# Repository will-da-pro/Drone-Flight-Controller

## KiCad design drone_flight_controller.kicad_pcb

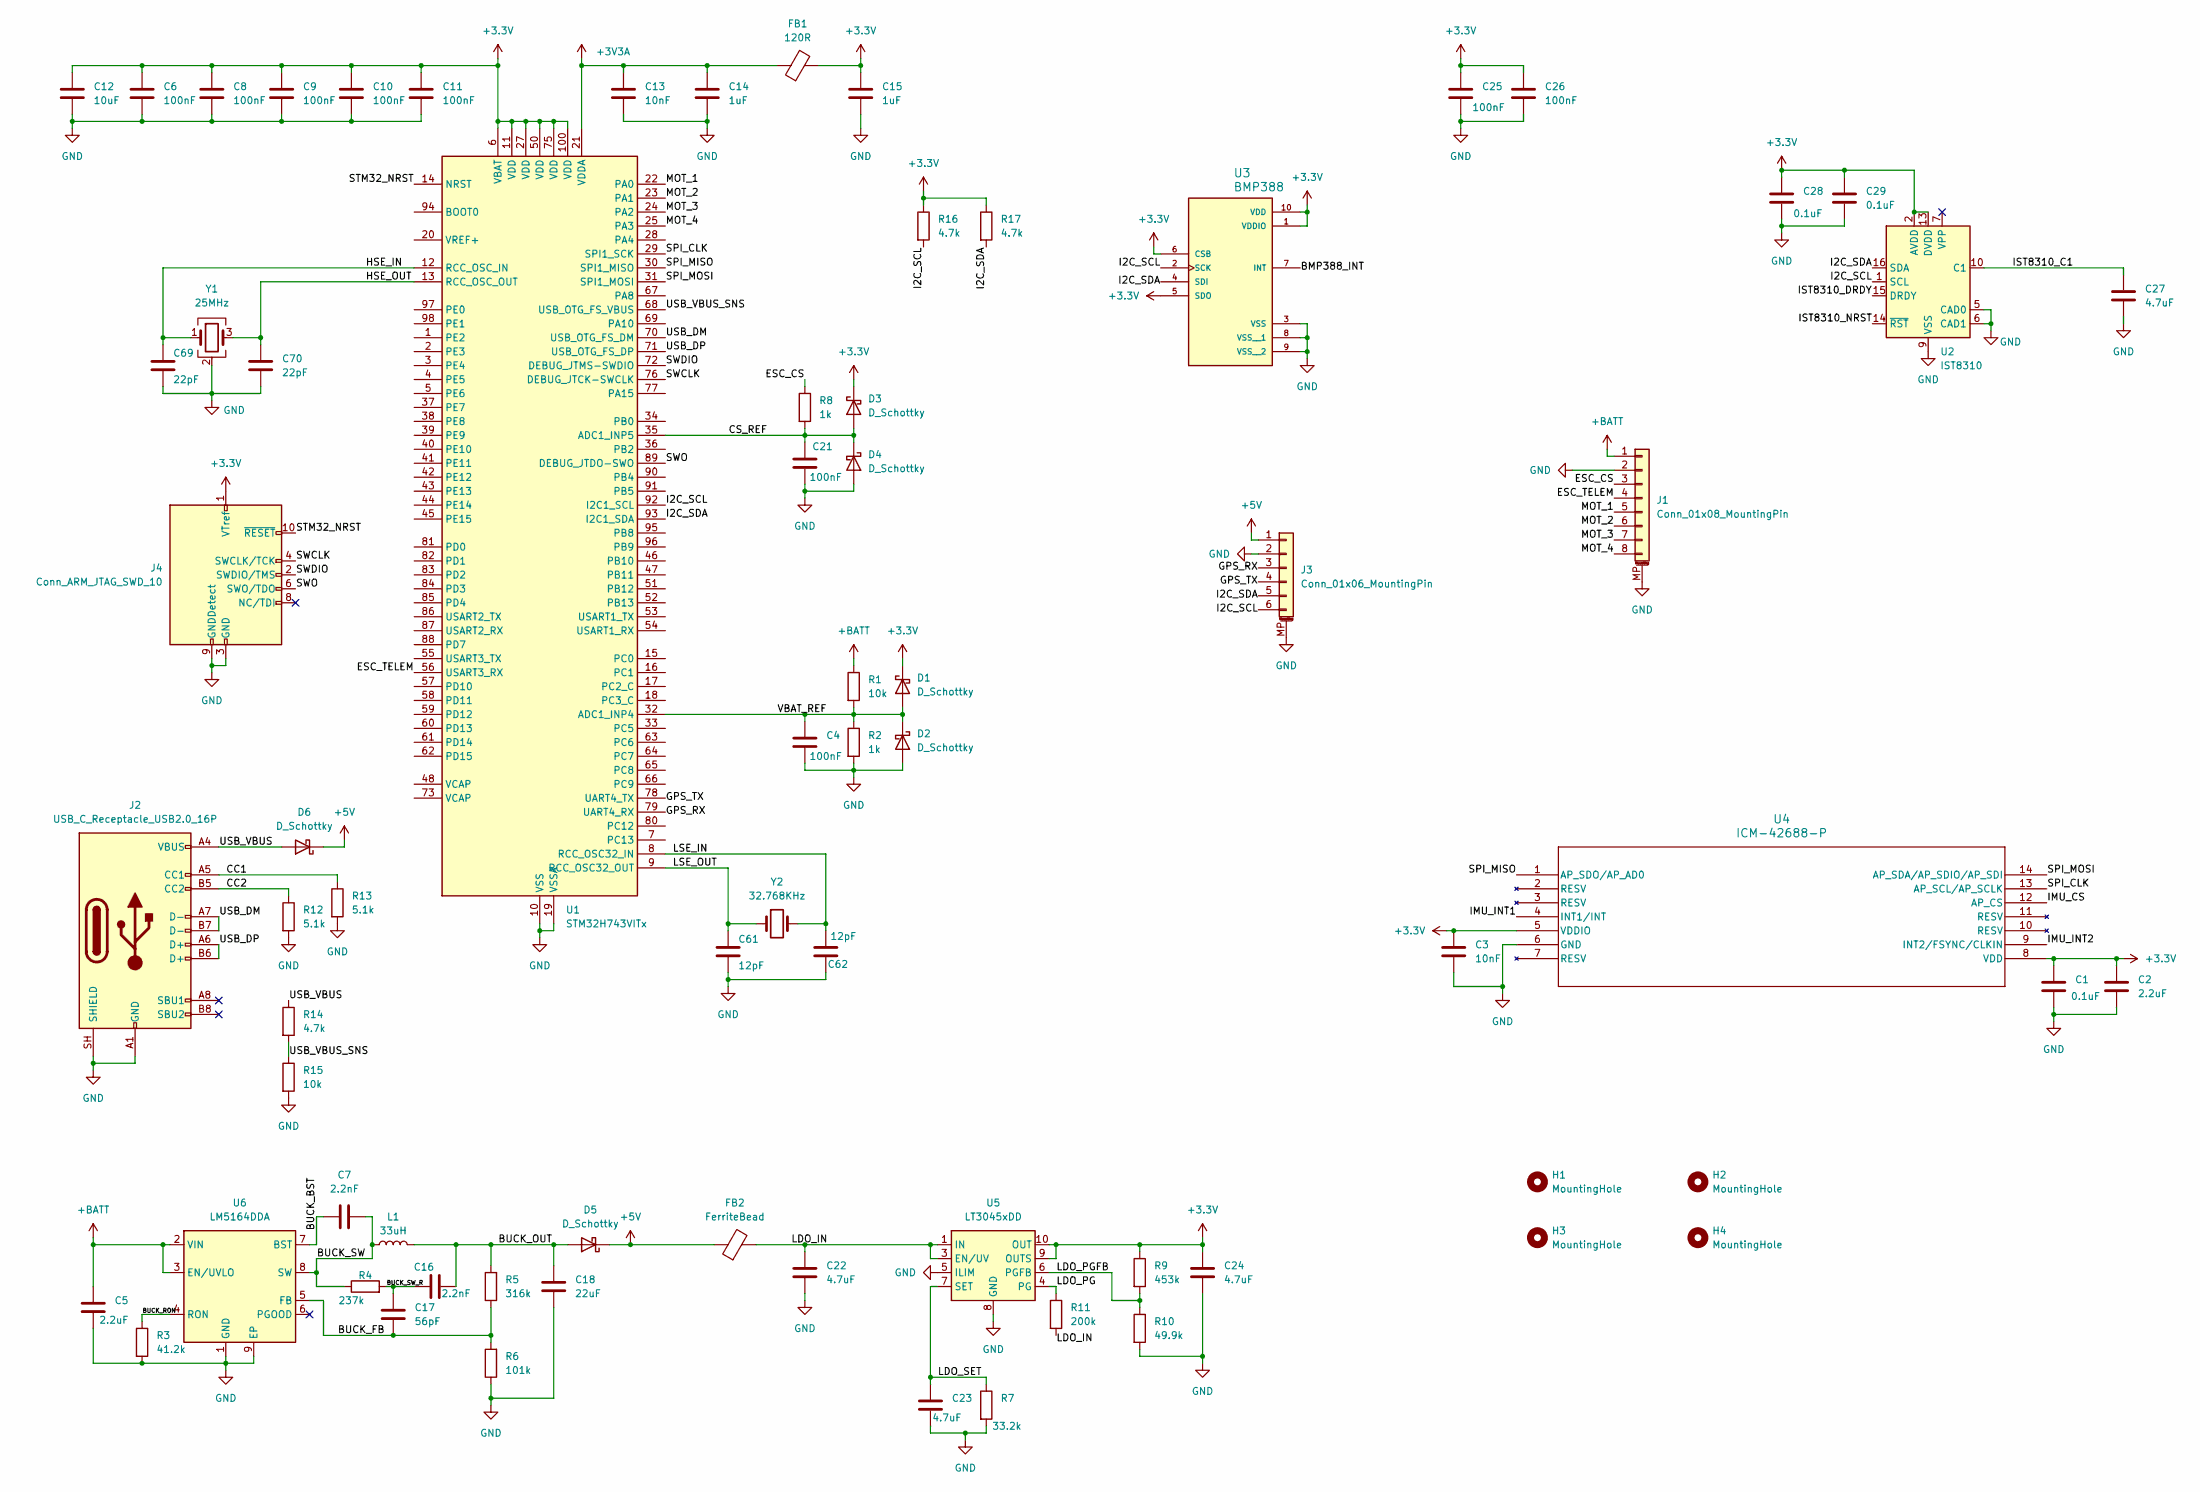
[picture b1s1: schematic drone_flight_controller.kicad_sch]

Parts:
C1, C28, C29: 0.1uF; C_0402_1005Metric
C2, C5: 2.2uF; C_0402_1005Metric
C3: 10nF; C_0402_1005Metric
C4, C21, C25, C26: 100nF; C_0402_1005Metric
C6, C8, C9, C10, C11: 100nF; C_0402_1005Metric; LCSC C307331
C7, C16: 2.2nF; C_0402_1005Metric
C12: 10uF; C_0603_1608Metric; LCSC C96446
C13: 10nF; C_0402_1005Metric; LCSC C15195
C14, C15: 1uF; C_0402_1005Metric; LCSC C52923
C17: 56pF; C_0402_1005Metric
C18: 22uF; C_0603_1608Metric
C22, C24: 4.7uF; C_0603_1608Metric
C23, C27: 4.7uF; C_0402_1005Metric
C61, C62: 12pF; C_0402_1005Metric; LCSC C76948
C69, C70: 22pF; C_0402_1005Metric; LCSC C76960
D1, D2, D3, D4: D_Schottky; D_0402_1005Metric
D5, D6: D_Schottky; D_SOD-123
FB1: 120R; L_0603_1608Metric; LCSC C113030
FB2: FerriteBead; L_0603_1608Metric
H1, H2, H3, H4: MountingHole; MountingHole_2.2mm_M2
J1: Conn_01x08_MountingPin; JST_SH_SM08B-SRSS-TB_1x08-1MP_P1.00mm_Horizontal
J2: USB_C_Receptacle_USB2.0_16P; USB_C_Receptacle_GCT_USB4085
J3: Conn_01x06_MountingPin; JST_SH_SM06B-SRSS-TB_1x06-1MP_P1.00mm_Horizontal
J4: Conn_ARM_JTAG_SWD_10; PinHeader_2x05_P1.27mm_Vertical
L1: 33uH; L_Vishay_IHLP-2525
R1, R15: 10k; R_0402_1005Metric
R2, R8: 1k; R_0402_1005Metric
R3: 41.2k; R_0402_1005Metric
R4: 237k; R_0402_1005Metric
R5: 316k; R_0402_1005Metric
R6: 101k; R_0402_1005Metric
R7: 33.2k; R_0402_1005Metric
R9: 453k; R_0402_1005Metric
R10: 49.9k; R_0402_1005Metric
R11: 200k; R_0402_1005Metric
R12, R13: 5.1k; R_0402_1005Metric
R14, R16, R17: 4.7k; R_0402_1005Metric
U1: STM32H743VITx; LQFP-100_14x14mm_P0.5mm
U2: IST8310; LGA-16_3x3mm_P0.5mm
U3: BMP388; XDCR_BMP388; PARTREV 1.7
U4: ICM-42688-P; LGA-14_3x2.5mm_P0.5mm_LayoutBorder3x4y
U5: LT3045xDD; DFN-10-1EP_3x3mm_P0.5mm_EP1.65x2.38mm
U6: LM5164DDA; HSOP-8-1EP_3.9x4.9mm_P1.27mm_EP2.41x3.1mm_ThermalVias
Y1: 25MHz; Crystal_SMD_3225-4Pin_3.2x2.5mm; LCSC C5444544
Y2: 32.768KHz; Crystal_SMD_3215-2Pin_3.2x1.5mm; LCSC C99010

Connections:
+3.3V: C1.1, C2.1, C3.1, C6.1, C8.1, C9.1, C10.1, C11.1, C12.1, C15.1, C24.1, C25.1, C26.1, C28.1, C29.1, D1.1 (K), D3.1 (K), FB1.2, J4.1 (VTref), R9.1, R16.1, R17.1, U1.6 (VBAT), U1.11 (VDD), U1.27 (VDD), U1.50 (VDD), U1.75 (VDD), U1.100 (VDD), U2.2 (AVDD), U2.13 (DVDD), U3.1 (VDDIO), U3.5 (SDO), U3.6 (CSB), U3.10 (VDD), U4.5 (VDDIO), U4.8 (VDD), U5.9 (OUTS), U5.10 (OUT)
+3V3A: C13.1, C14.1, FB1.1, U1.21 (VDDA)
+5V: D5.1 (K), D6.1 (K), FB2.1, J3.1
+BATT: C5.1, J1.1, R1.1, U6.2 (VIN), U6.3 (EN/UVLO)
/BMP388_INT: U3.7 (INT)
/BUCK_BST: C7.1, U6.7 (BST)
/BUCK_FB: C17.1, R5.1, R6.2, U6.5 (FB)
/BUCK_OUT: C16.2, C18.2, D5.2 (A), L1.2, R5.2
/BUCK_RON: R3.1, U6.4 (RON)
/BUCK_SW: C7.2, L1.1, R4.1, U6.8 (SW)
/BUCK_SW_R: C16.1, C17.2, R4.2
/CC1: J2.A5 (CC1), R13.1
/CC2: J2.B5 (CC2), R12.1
/CS_REF: C21.1, D3.2 (A), D4.1 (K), R8.2, U1.35 (ADC1_INP5)
/ESC_CS: J1.3, R8.1
/ESC_TELEM: J1.4, U1.56 (USART3_RX)
/GPS_RX: J3.3, U1.79 (UART4_RX)
/GPS_TX: J3.4, U1.78 (UART4_TX)
/HSE_IN: C69.1, U1.12 (RCC_OSC_IN), Y1.1
/HSE_OUT: C70.1, U1.13 (RCC_OSC_OUT), Y1.3
/I2C_SCL: J3.6, R16.2, U1.92 (I2C1_SCL), U2.1 (SCL), U3.2 (SCK)
/I2C_SDA: J3.5, R17.2, U1.93 (I2C1_SDA), U2.16 (SDA), U3.4 (SDI)
/IMU_CS: U4.12 (AP_CS)
/IMU_INT1: U4.4 (INT1/INT)
/IMU_INT2: U4.9 (INT2/FSYNC/CLKIN)
/IST8310_C1: C27.1, U2.10 (C1)
/IST8310_DRDY: U2.15 (DRDY)
/IST8310_NRST: U2.14 (~RST)
/LDO_IN: C22.1, FB2.2, R11.2, U5.1 (IN), U5.2 (IN), U5.3 (EN/UV)
/LDO_PG: R11.1, U5.4 (PG)
/LDO_PGFB: R9.2, R10.1, U5.6 (PGFB)
/LDO_SET: C23.1, R7.1, U5.7 (SET)
/LSE_IN: C62.1, U1.8 (RCC_OSC32_IN), Y2.2
/LSE_OUT: C61.1, U1.9 (RCC_OSC32_OUT), Y2.1
/MOT_1: J1.5, U1.22 (PA0)
/MOT_2: J1.6, U1.23 (PA1)
/MOT_3: J1.7, U1.24 (PA2)
/MOT_4: J1.8, U1.25 (PA3)
/SPI_CLK: U1.29 (SPI1_SCK), U4.13 (AP_SCL/AP_SCLK)
/SPI_MISO: U1.30 (SPI1_MISO), U4.1 (AP_SDO/AP_AD0)
/SPI_MOSI: U1.31 (SPI1_MOSI), U4.14 (AP_SDA/AP_SDIO/AP_SDI)
/STM32_NRST: J4.10 (~RESET), U1.14 (NRST)
/SWCLK: J4.4 (SWCLK/TCK), U1.76 (DEBUG_JTCK-SWCLK)
/SWDIO: J4.2 (SWDIO/TMS), U1.72 (DEBUG_JTMS-SWDIO)
/SWO: J4.6 (SWO/TDO), U1.89 (DEBUG_JTDO-SWO)
/USB_DM: J2.A7 (D-), J2.B7 (D-), U1.70 (USB_OTG_FS_DM)
/USB_DP: J2.A6 (D+), J2.B6 (D+), U1.71 (USB_OTG_FS_DP)
/USB_VBUS: D6.2 (A), J2.A4 (VBUS), J2.A9 (VBUS), J2.B4 (VBUS), J2.B9 (VBUS), R14.1
/USB_VBUS_SNS: R14.2, R15.1, U1.68 (USB_OTG_FS_VBUS)
/VBAT_REF: C4.1, D1.2 (A), D2.1 (K), R1.2, R2.1, U1.32 (ADC1_INP4)
GND: C1.2, C2.2, C3.2, C4.2, C5.2, C6.2, C8.2, C9.2, C10.2, C11.2, C12.2, C13.2, C14.2, C15.2, C18.1, C21.2, C22.2, C23.2, C24.2, C25.2, C26.2, C27.2, C28.2, C29.2, C61.2, C62.2, C69.2, C70.2, D2.2 (A), D4.2 (A), J1.2, J1.MP (MountPin), J2.A1 (GND), J2.A12 (GND), J2.B1 (GND), J2.B12 (GND), J2.SH (SHIELD), J3.2, J3.MP (MountPin), J4.3 (GND), J4.5 (GND), J4.9 (GNDDetect), R2.2, R3.2, R6.1, R7.2, R10.2, R12.2, R13.2, R15.2, U1.10 (VSS), U1.19 (VSSA), U1.26 (VSS), U1.49 (VSS), U1.74 (VSS), U1.99 (VSS), U2.5 (CAD0), U2.6 (CAD1), U2.9 (VSS), U2.11 (VSS), U3.3 (VSS), U3.8 (VSS__1), U3.9 (VSS__2), U4.6 (GND), U5.5 (ILIM), U5.8 (GND), U5.11 (GND), U6.1 (GND), U6.9 (EP), Y1.2 (G), Y1.4 (G)

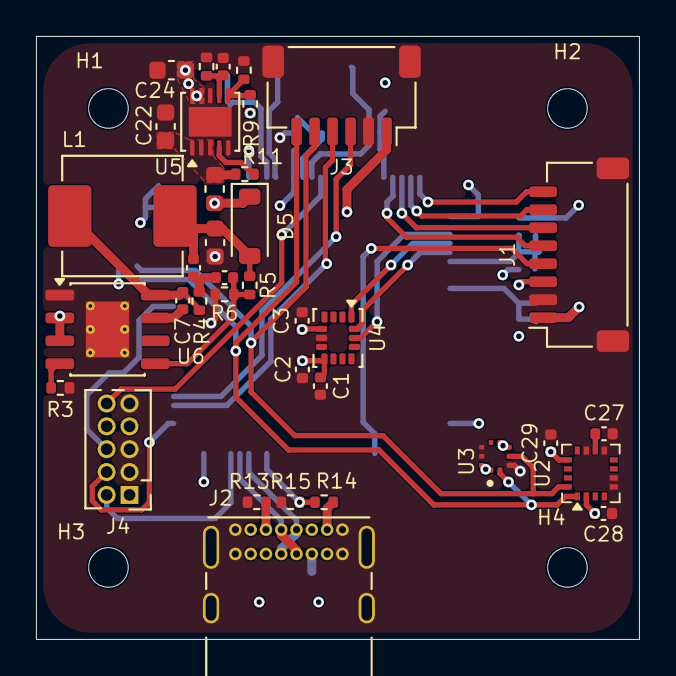
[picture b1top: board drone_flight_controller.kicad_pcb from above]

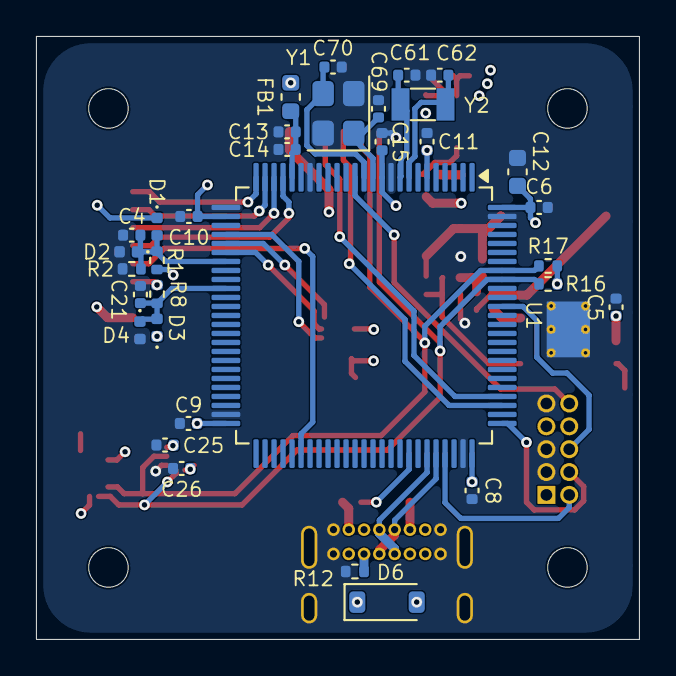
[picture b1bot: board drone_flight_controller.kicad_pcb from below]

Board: 4 copper layers, 33.5 x 33.5 mm, 73 parts (33 on the bottom side), 45 nets.
